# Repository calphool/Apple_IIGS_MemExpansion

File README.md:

# Apple_IIGS_MemExpansion

Collection area for my Apple IIGS Memory Expansion board.

Build History
-------------

April 28, 2019

Eaglecad drawings should be complete now.  Off to the fab house...

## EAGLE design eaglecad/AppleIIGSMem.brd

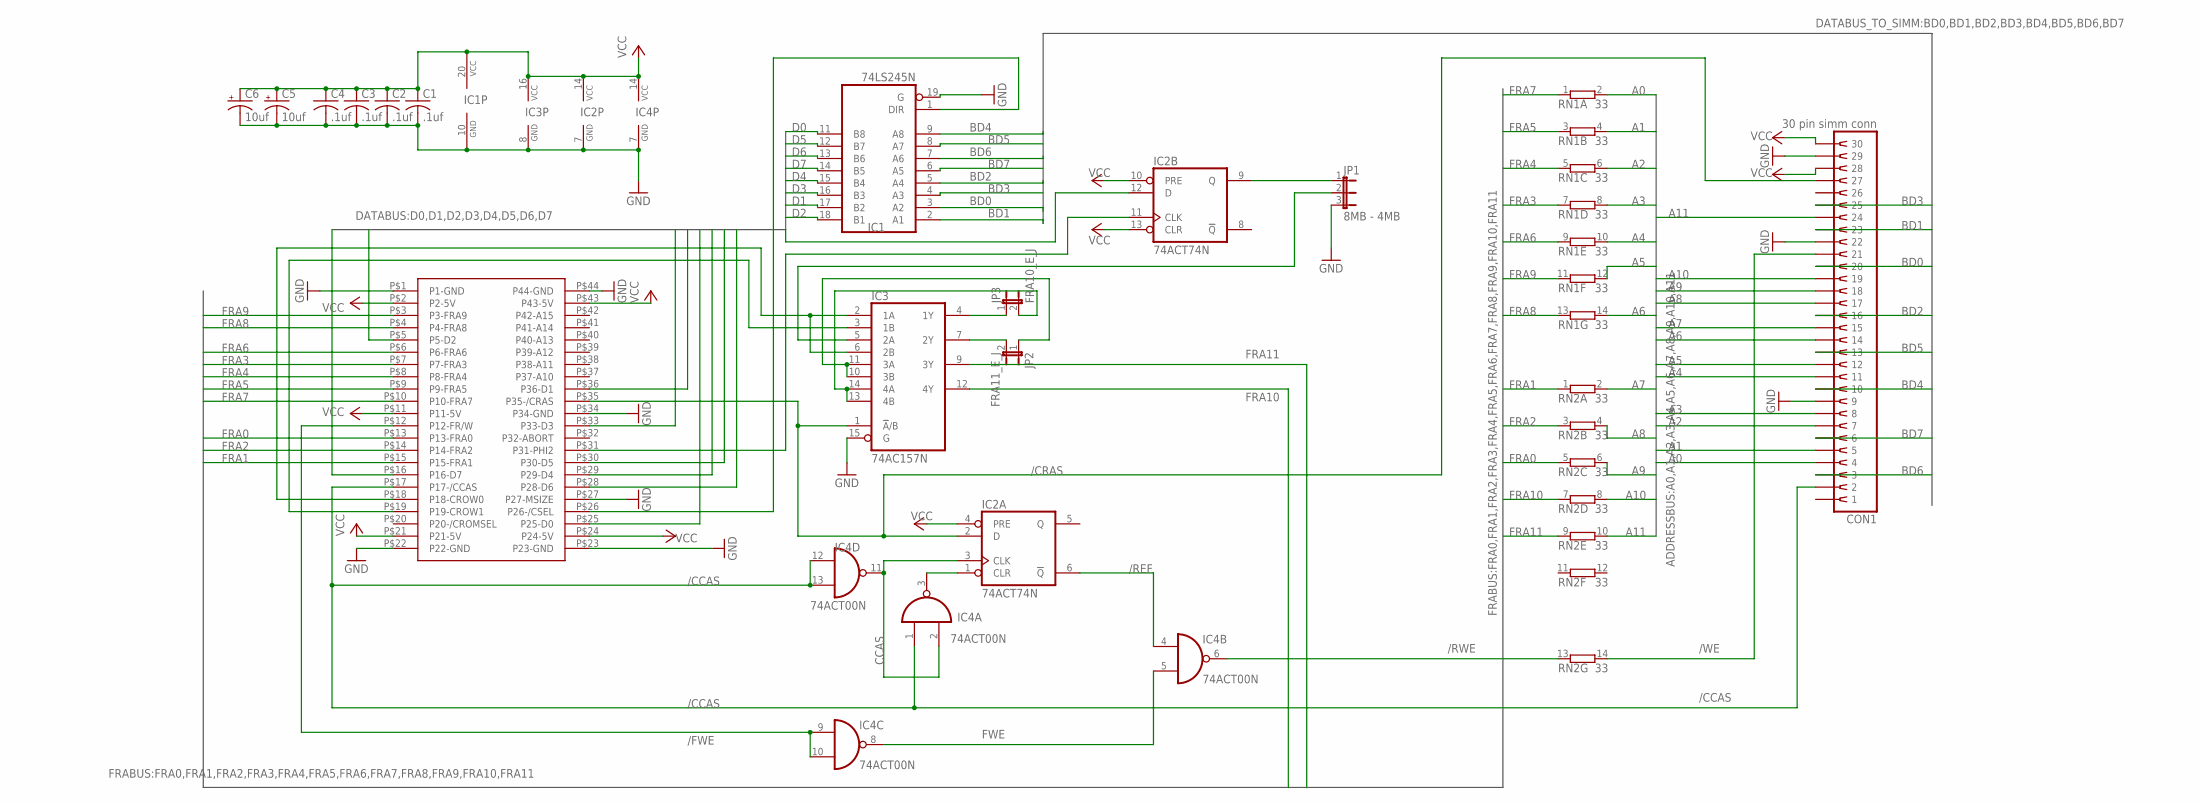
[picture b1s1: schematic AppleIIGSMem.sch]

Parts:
C1, C2, C3, C4: .1uf; C025-025X050
C5, C6: 10uf; E2,5-5
CON1: 30 pin simm conn; SIMM30
IC1: 74LS245N; DIL20
IC2: 74ACT74N; DIL14
IC3: 74AC157N; DIL16
IC4: 74ACT00N; DIL14
JP1: 8MB - 4MB; JP2
JP2: FRA11_E_J; JP1
JP3: FRA10_E_J; JP1
RN1, RN2: 33; SIL14
U$1: APPLE_IIGS_MEM_EXP_CARD_EDGE; EDGE_FINGERS

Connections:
74CLR1: IC2.1 (CLR), IC4.3 (O)
/CCAS: CON1.2, IC4.1 (I0), IC4.12 (I0), IC4.13 (I1), U$1.P$17 (P17-/CCAS)
/CRAS: CON1.27, IC2.2 (D), IC3.1 (!A!/B), U$1.P$35 (P35-/CRAS)
/CSEL: IC1.1 (DIR), U$1.P$26 (P26-/CSEL)
/FWE: IC4.9 (I0), IC4.10 (I1), U$1.P$12 (P12-FR/W)
/REF: IC2.6 (!Q), IC4.4 (I0)
/RWE: IC4.6 (O), RN2.13 (1)
/WE: CON1.21, RN2.14 (2)
A0: CON1.4, RN1.2
A1: CON1.5, RN1.4 (2)
A2: CON1.7, RN1.6 (2)
A3: CON1.8, RN1.8 (2)
A4: CON1.11, RN1.10 (2)
A5: CON1.12, RN1.12 (2)
A6: CON1.14, RN1.14 (2)
A7: CON1.15, RN2.2
A8: CON1.17, RN2.4 (2)
A9: CON1.18, RN2.6 (2)
A10: CON1.19, RN2.8 (2)
A11: CON1.24, RN2.10 (2)
BD0: CON1.20, IC1.3 (A2)
BD1: CON1.23, IC1.2 (A1)
BD2: CON1.16, IC1.5 (A4)
BD3: CON1.25, IC1.4 (A3)
BD4: CON1.10, IC1.9 (A8)
BD5: CON1.13, IC1.8 (A7)
BD6: CON1.3, IC1.7 (A6)
BD7: CON1.6, IC1.6 (A5)
CCAS: IC2.3 (CLK), IC4.2 (I1), IC4.11 (O)
CROW0: IC3.2 (1A), IC3.6 (2B), U$1.P$18 (P18-CROW0)
CROW1: IC3.3 (1B), U$1.P$19 (P19-CROW1)
CROW2: IC3.5 (2A), JP1.2
D0: IC1.11 (B8), U$1.P$25 (P25-D0)
D1: IC1.17 (B2), U$1.P$36 (P36-D1)
D2: IC1.18 (B1), U$1.P$5 (P5-D2)
D3: IC1.16 (B3), U$1.P$33 (P33-D3)
D4: IC1.15 (B4), U$1.P$29 (P29-D4)
D5: IC1.12 (B7), U$1.P$30 (P30-D5)
D6: IC1.13 (B6), IC2.12 (D), U$1.P$28 (P28-D6)
D7: IC1.14 (B5), U$1.P$16 (P16-D7)
FRA0: RN2.5 (1), U$1.P$13 (P13-FRA0)
FRA1: RN2.1, U$1.P$15 (P15-FRA1)
FRA2: RN2.3 (1), U$1.P$14 (P14-FRA2)
FRA3: RN1.7 (1), U$1.P$7 (P7-FRA3)
FRA4: RN1.5 (1), U$1.P$8 (P8-FRA4)
FRA5: RN1.3 (1), U$1.P$9 (P9-FRA5)
FRA6: RN1.9 (1), U$1.P$6 (P6-FRA6)
FRA7: RN1.1, U$1.P$10 (P10-FRA7)
FRA8: RN1.13 (1), U$1.P$4 (P4-FRA8)
FRA9: RN1.11 (1), U$1.P$3 (P3-FRA9)
FRA10: IC3.12 (4Y), RN2.7 (1)
FRA10_E: IC3.4 (1Y), JP3.1
FRA11: IC3.9 (3Y), RN2.9 (1)
FRA11_E: IC3.7 (2Y), JP2.2
FWE: IC4.5 (I1), IC4.8 (O)
GND: C1.2, C2.2, C3.2, C4.2, C5.-, C6.-, CON1.9, CON1.22, CON1.29, IC1.10 (GND), IC1.19 (G), IC2.7 (GND), IC3.8 (GND), IC3.15 (G), IC4.7 (GND), JP1.3, U$1.P$1 (P1-GND), U$1.P$22 (P22-GND), U$1.P$23 (P23-GND), U$1.P$27 (P27-MSIZE), U$1.P$34 (P34-GND), U$1.P$44 (P44-GND)
unnamed: IC2.9 (Q), JP1.1
unnamed: IC3.10 (3B), IC3.11 (3A), JP2.1
unnamed: IC3.13 (4B), IC3.14 (4A), JP3.2
PHI2: IC2.11 (CLK), U$1.P$31 (P31-PHI2)
VCC: C1.1, C2.1, C3.1, C4.1, C5.+, C6.+, CON1.28, CON1.30, IC1.20 (VCC), IC2.4 (PRE), IC2.10 (PRE), IC2.13 (CLR), IC2.14 (VCC), IC3.16 (VCC), IC4.14 (VCC), U$1.P$2 (P2-5V), U$1.P$11 (P11-5V), U$1.P$21 (P21-5V), U$1.P$24 (P24-5V), U$1.P$43 (P43-5V)

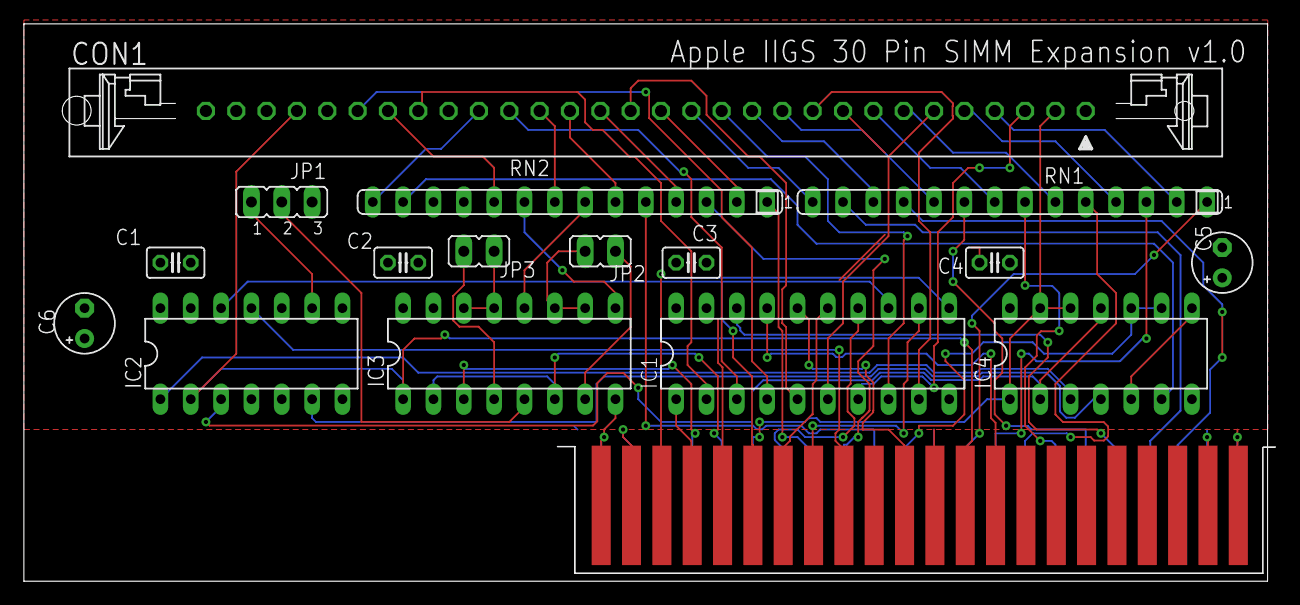
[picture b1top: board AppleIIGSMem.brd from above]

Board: 2 copper layers, 104.7 x 46.5 mm, 17 parts (0 on the bottom side), 61 nets.

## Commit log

2019-04-28 initial upload
